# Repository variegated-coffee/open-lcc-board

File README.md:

# Open LCC Board

Schematics and PCB files for the main Open LCC hardware. Licensed under the CERN OHL-P license.

This is an evolution of [magnusnordlander/smart-lcc](https://github.com/magnusnordlander/smart-lcc).

## Disclaimer

Anything you do with this, you do at your own risk. Components have been fried already during the course of this project. Your machine uses both line voltage power, high pressured hot water, steam and other dangerous components. Risks include but are not limited to, damaging the machine, personal injury, property damage and summoning dead Cthulhu from his sleep at R'lyeh.

## Architecture and feature set

* RP2040 MCU communicating over UART with the Control Board
  * 2 MB Program Flash
  * 2 MB Settings Flash
  * Micro SD Card Slot
  * 2x QWIIC expansion ports
* ESP32-S3-WROOM-1U-N16R8 MCU
  * Connector for SSD1309 128x64px OLED display (only one display can be used at a time)
  * Solder pads for ST9987V 1.47" Round Rectangle TFT display (only one display can be used at a time)
  * Two push buttons
  * 1x QWIIC expansion port
  * Antenna connector (Espresso machines are basically faraday cages, so an external antenna is a good idea)
* 5 wire bus between RP2040 and ESP32-S3
	* RX, TX, CTS, RTS, Serial Boot
* Debug port
  * Exposes RP2040 USB, RP2040 SWD, RP2040 BOOTSEL, RP2040 ~RESET, ESP32 USB, ESP32 JTAG, ESP32 GPIO0, ESP32 EN and power rails.

## Hardware revisions

### Smart LCC (various revisions, not maintained in this repository)

The earliest revisions of this board. Based around Arduino RP2040 Nano.

### R1A (r1a branch)

This design is NOT RECOMMENDED for any purpose. It relies on the Control Board providing 3V3 to the board, but the Control Board is not able to supply enough power. As such, it *does not work as intended*. 

It is however a major redesign from the Smart LCC, and added most of the features described above.

### R2A (r2a branch)

Latest manufactured revision, though if you want one of the boards, you may want to wait for R2B.

#### Changes from R1A

* Added I2C pull-up resistors for QWIIC expansion ports
* Added on-board DC-DC converter to step down 12V to 3V3.
* Added back side connector for 1.47" TFT
* Moved test points for display connector to back side
* Added full bus to RP2040 settings flash (n.b. not the program flash), allowing for QSPI via PIO instead of regular SPI
* Added QWIIC expansion port to ESP32-S3
* Added Test Points for unused RP2040 GPIOs
* Removed 3V3_OLED from debug port

#### Errata

* The Schottky diodes do not provide adequate power supply reverse current protection. **DO NOT SUPPLY POWER FROM BOTH A DEBUG BOARD AND A CONTROL BOARD SIMULTANEOUSLY**
* It is unnecessary to connect both SD_DET_A and SD_DET_B to an MCU.

### R2B (r2b branch)

This revision hasn't been completely manufactured, and I don't intend to ever do that. I did order PCBs and verify the OR-ing controller subcircuit though, which is why there's now a R2C.

#### Changes from R2A

* Replaced the Schottky Diodes with two LM5050-1 OR-ing controllers.
* Connected SD card DET_A to GND, and removed the connection from the RP2040. 
* Widened traces and trace clearances, and added copper pours for improved manufacturability.

#### Errata

* The LM5050-1 and the MOSFET have reverse leakage currents totalling 0.6 mA. While this is unlikely to cause any issues in the real world, adding pulldown resistors seems prudent.

### R2C (main branch)

This revision hasn't been completely manufactured either (I'm running R2A in my machine), and as of writing, I don't have any plans to do so. Considering the small changes from R2B and R2A, which have been partially verified and fully verified respectively though, everything should work a treat.

#### Changes from R2B

* Added 18K7 pulldown resistors to the power supply rails.

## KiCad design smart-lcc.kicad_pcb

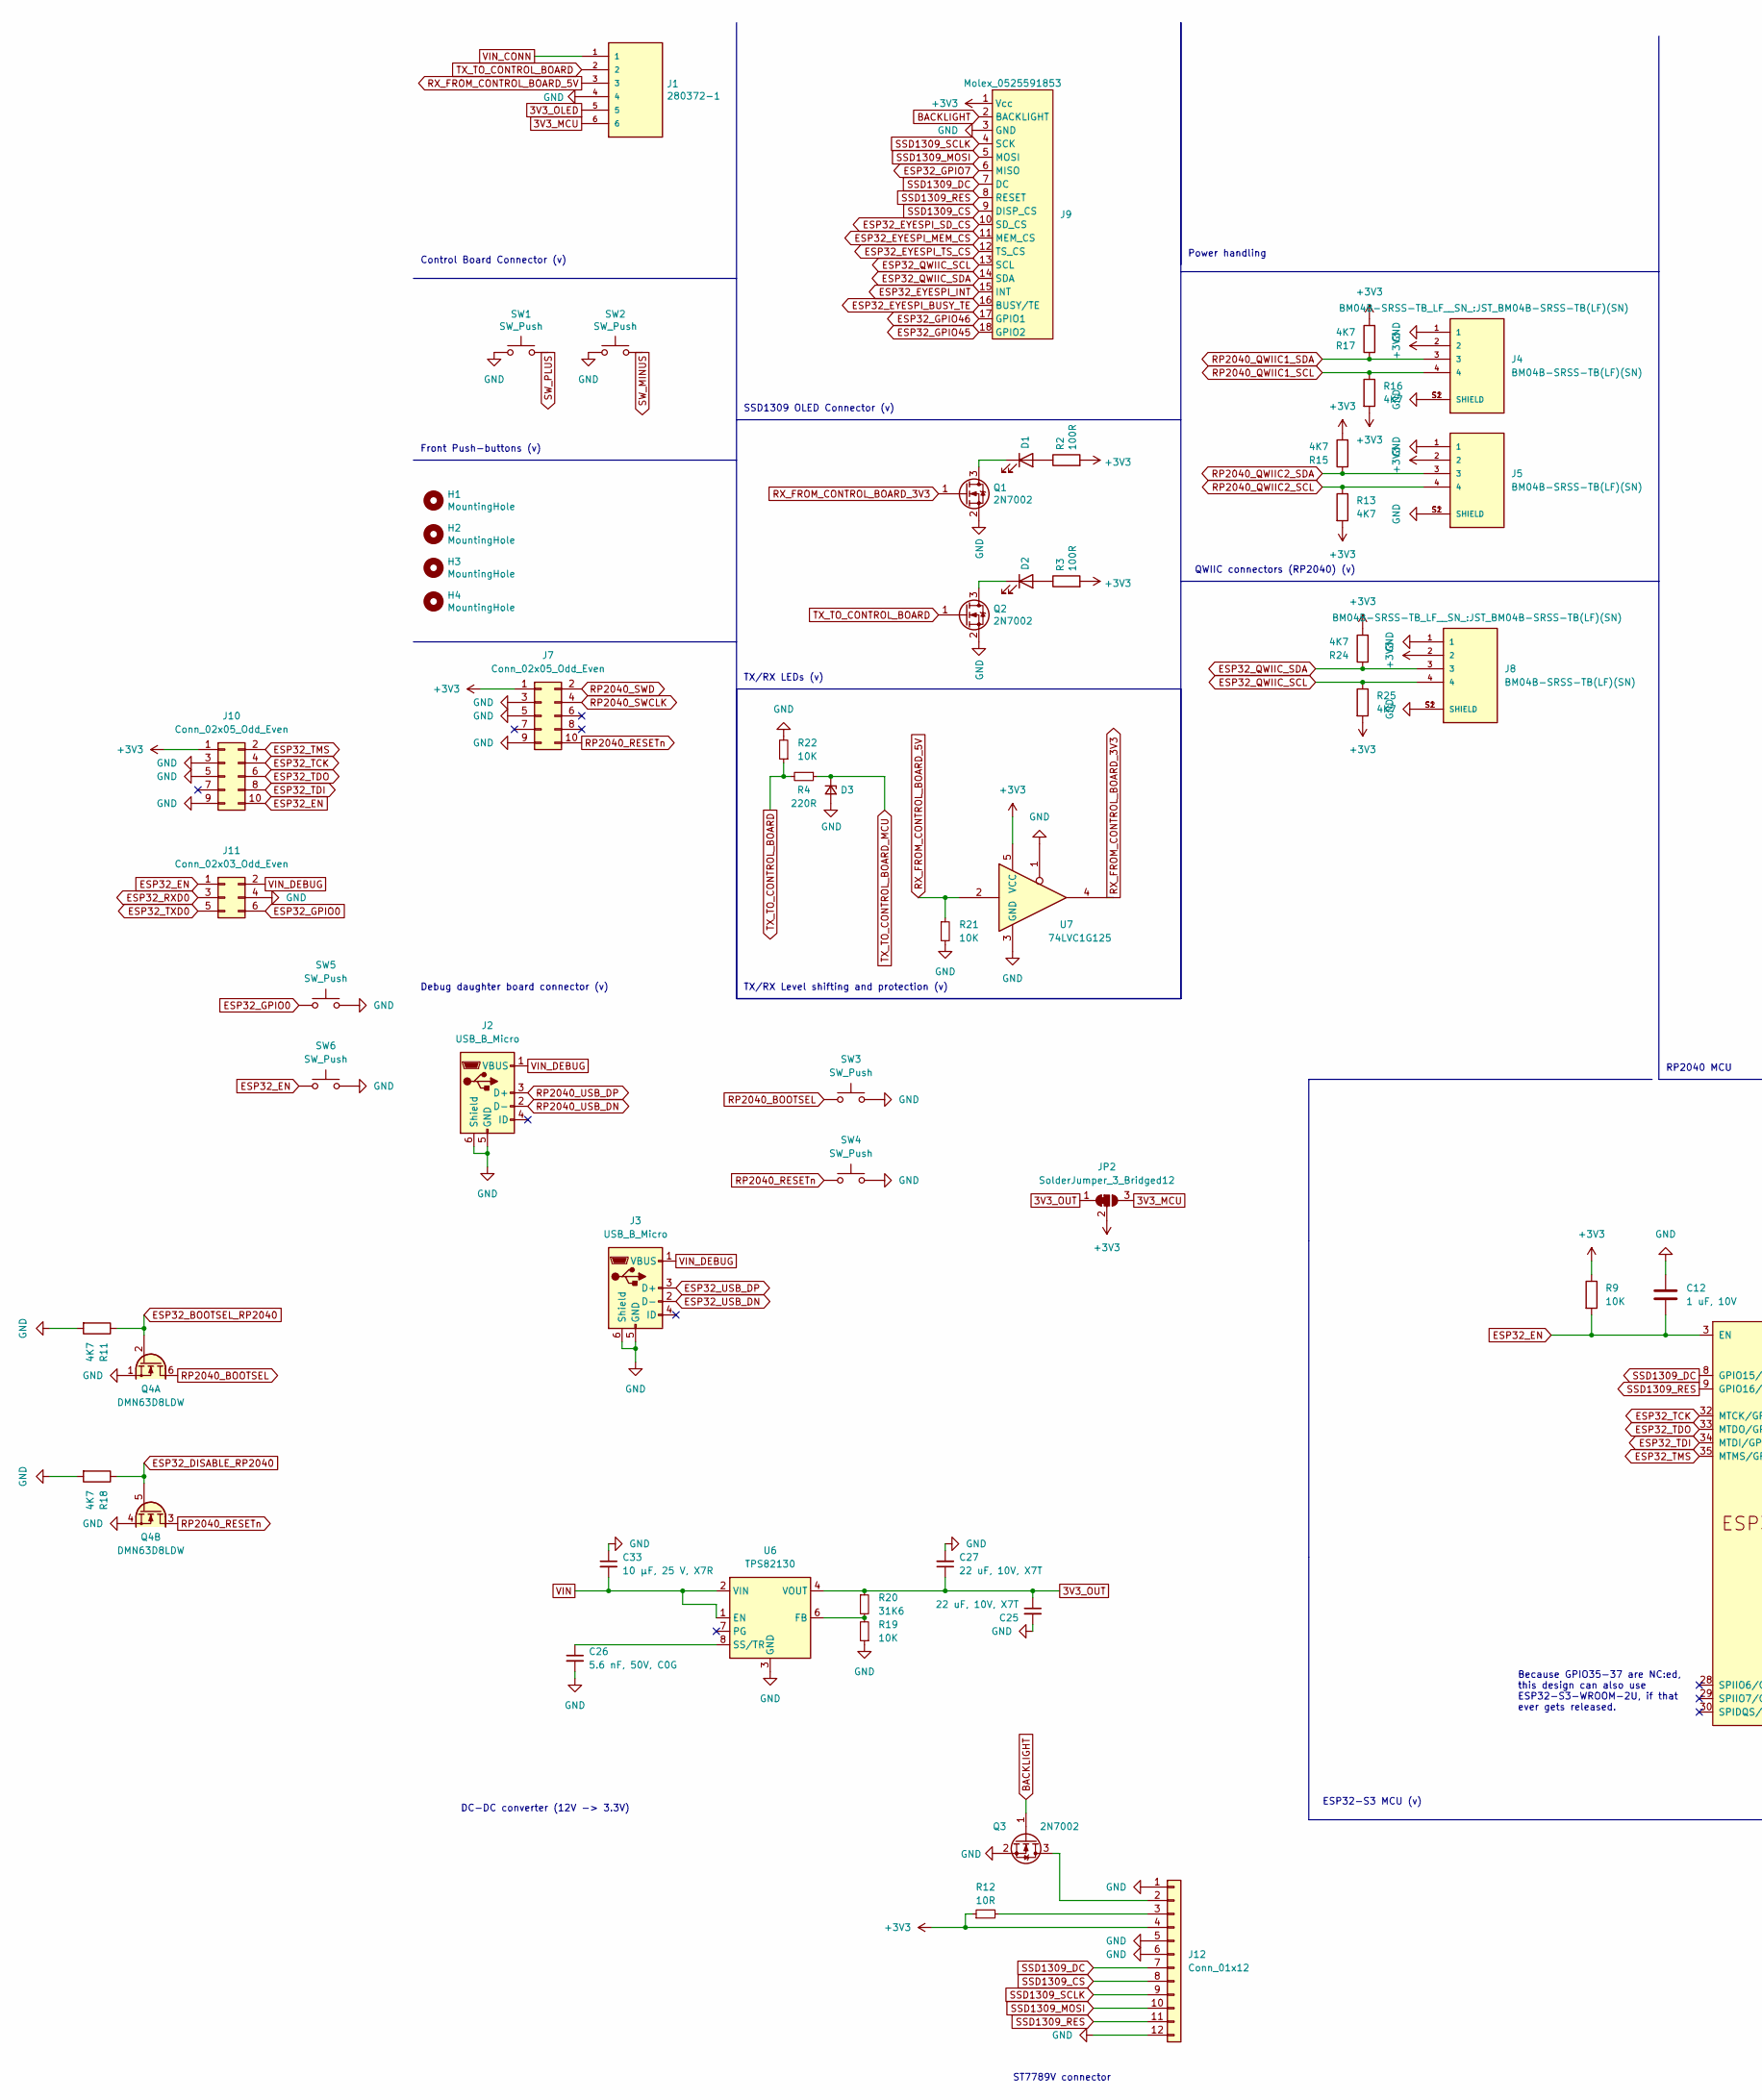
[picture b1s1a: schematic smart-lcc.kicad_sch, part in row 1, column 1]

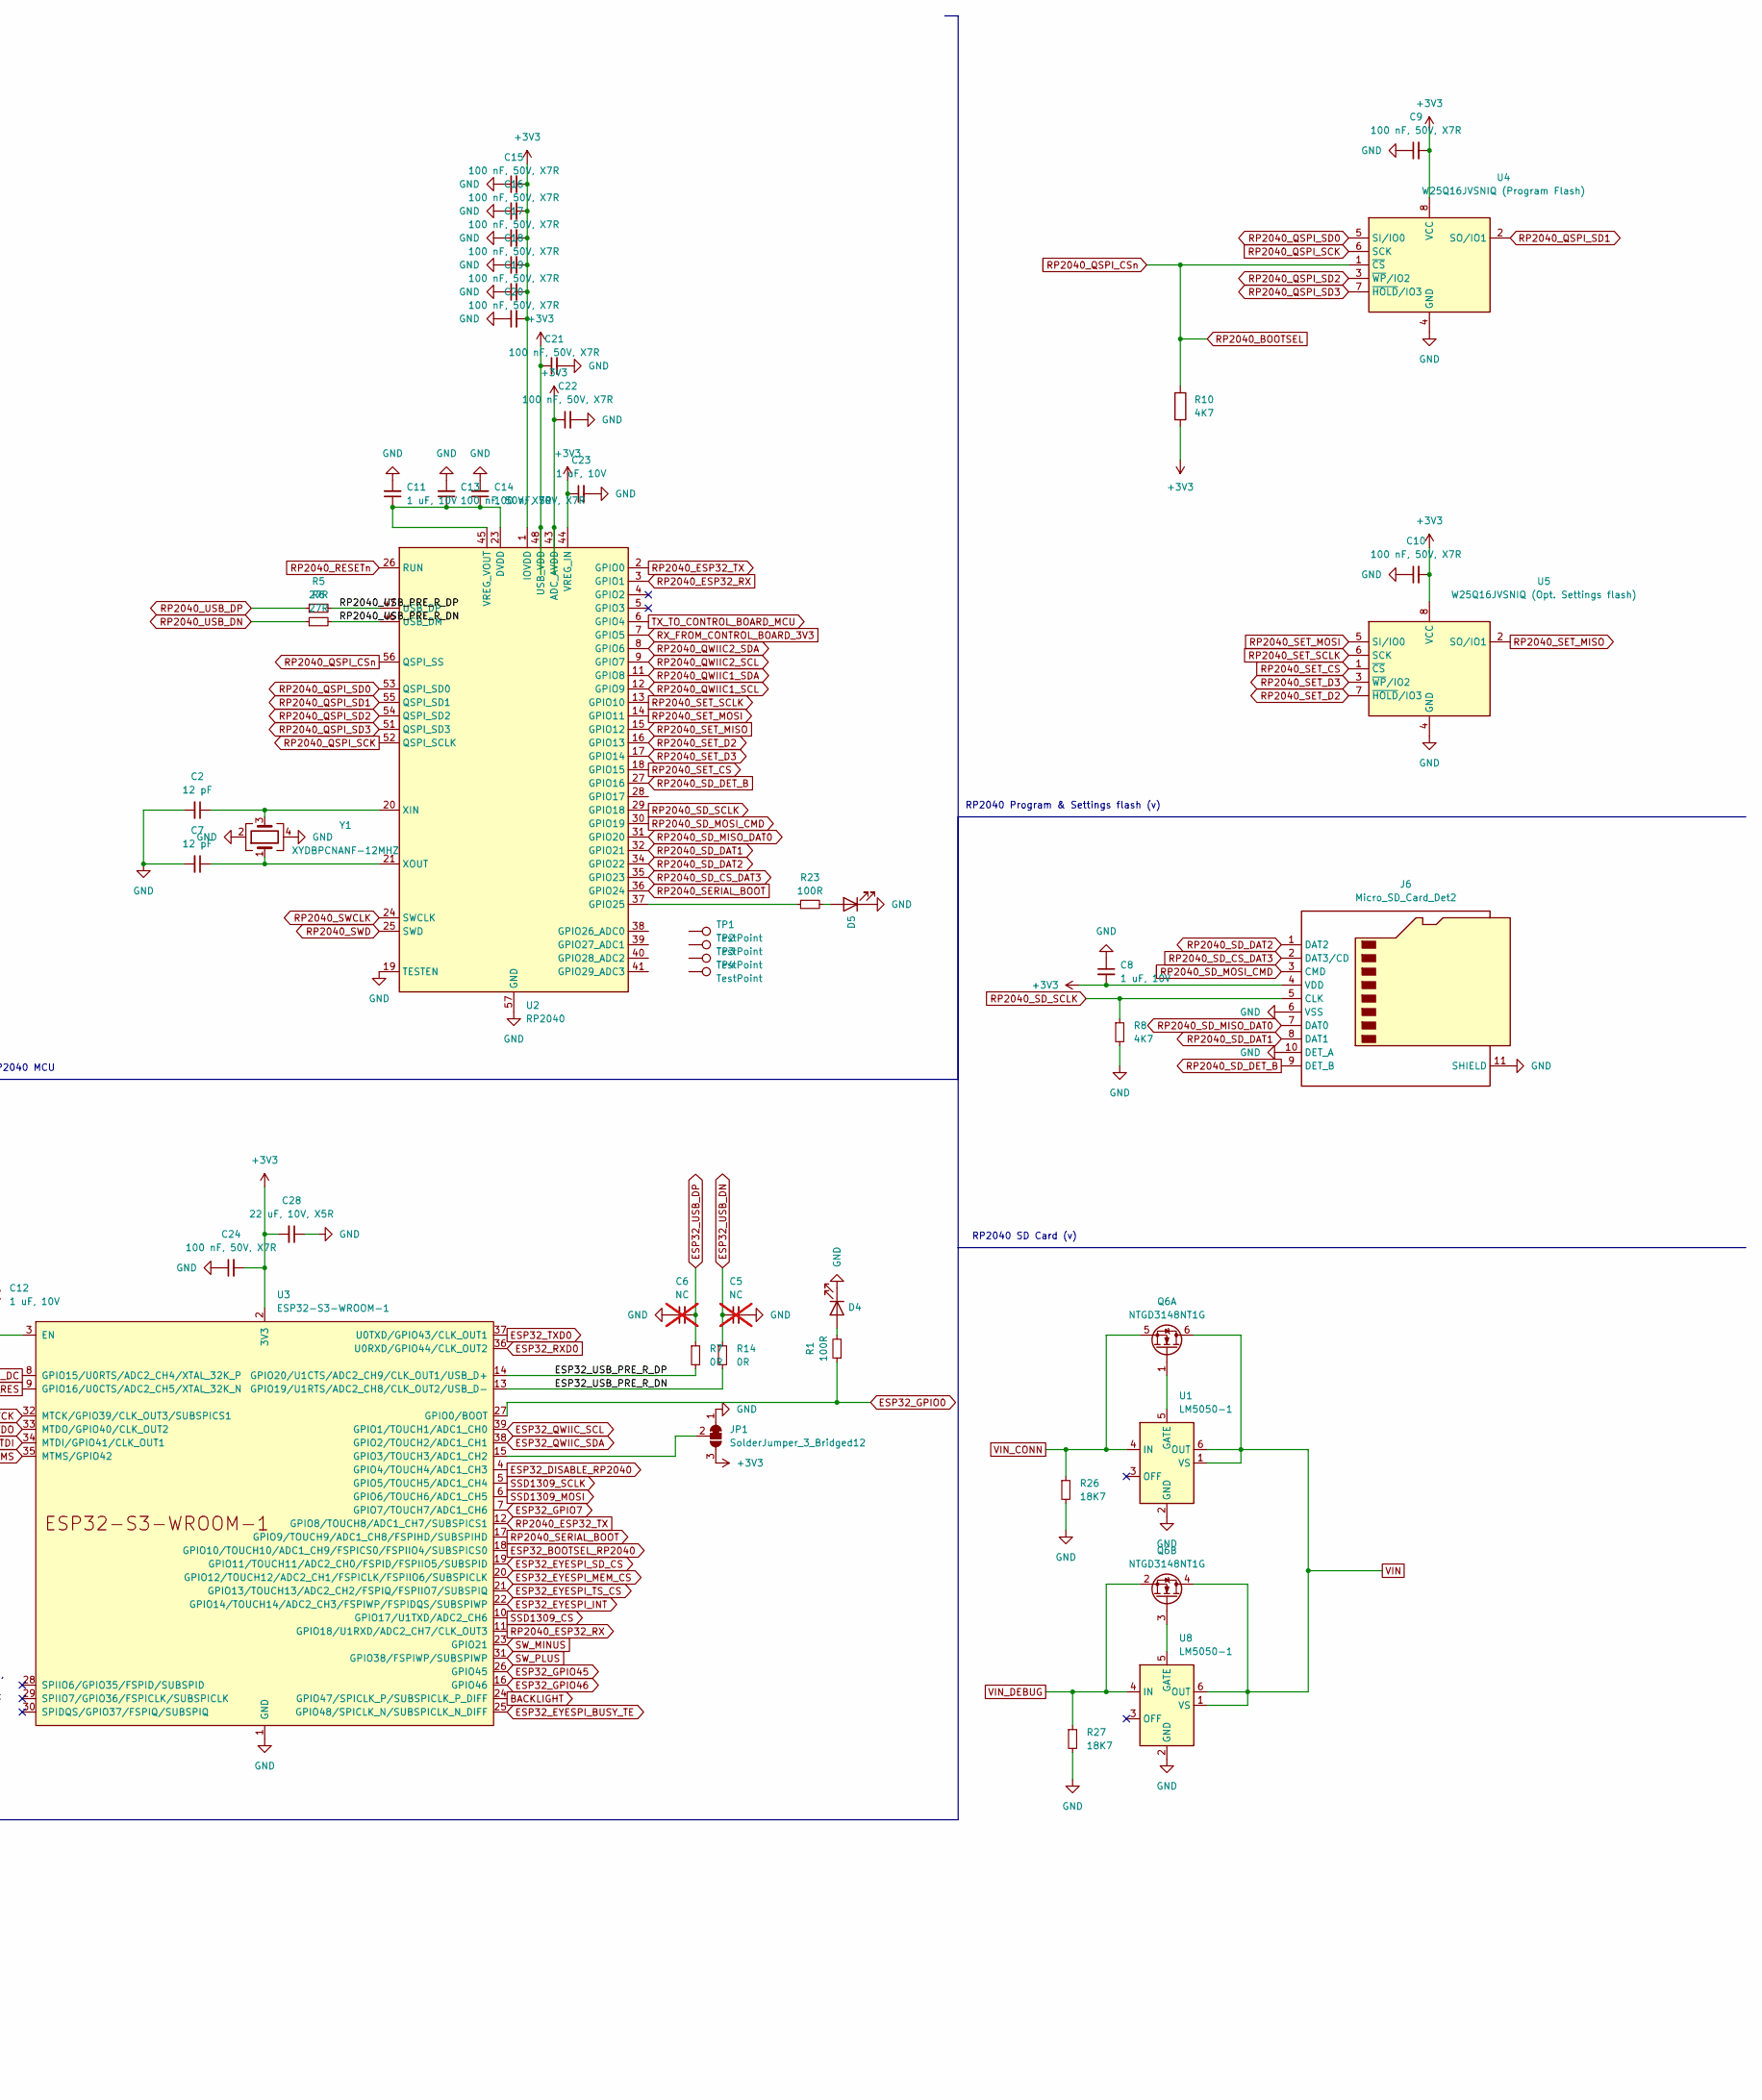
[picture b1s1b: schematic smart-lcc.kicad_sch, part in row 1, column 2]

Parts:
C2, C7: 12 pF; C_0402_1005Metric; LCSC C161527
C5, C6: NC; C_0402_1005Metric; not fitted
C8: 1 uF, 10V; C_0201_0603Metric; LCSC C426073
C9, C10, C13, C14, C15, C16, C17, C18, C19, C20, C21, C22, C24: 100 nF, 50V, X7R; C_0201_0603Metric; JLCPCB Basic N
C11, C12, C23: 1 uF, 10V; C_0201_0603Metric; JLCPCB Basic N
C25, C27: 22 uF, 10V, X7T; C_0805_2012Metric; LCSC C782176
C26: 5.6 nF, 50V, C0G; C_0402_1005Metric; LCSC C2976066
C28: 22 uF, 10V, X5R; C_0603_1608Metric; LCSC C2980159
C33: 10 μF, 25 V, X7R; C_1206_3216Metric; LCSC C2803388
D1, D2, D4, D5: 19-217/BHC-ZL1M2RY/3T; LED_0603_1608Metric; JLCPCB Basic Y
D3: TPZ3V6C-1006; D_SOD-882_DFN1006-2; JLCPCB Basic N
H1, H2, H3, H4: MountingHole; MountingHole_2.7mm
J1: 280372-1; TE_280372-1
J2, J3: USB_B_Micro; USB_Micro-B_Molex-105133-0001; LCSC C586226
J4, J5, J8: BM04B-SRSS-TB(LF)(SN); JST_BM04B-SRSS-TB(LF)(SN); PARTREV N/A; LCSC C160390
J6: Micro_SD_Card_Det2; microSD_HC_Hirose_DM3D-SF; JLCPCB Basic N
J7, J10: Conn_02x05_Odd_Even; PinHeader_2x05_P1.27mm_Vertical_SMD
J9: Molex_0525591853; CON_5051101892_MOL; LCSC C3169221
J11: Conn_02x03_Odd_Even; PinHeader_2x03_P1.27mm_Vertical_SMD
J12: Conn_01x12; TFT_1.47IN_172X320_12P
JP1: SolderJumper_3_Bridged12; SolderJumper-3_P1.3mm_Bridged2Bar12_RoundedPad1.0x1.5mm_Num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
JP2: SolderJumper_3_Bridged12; SolderJumper-3_P1.3mm_Bridged2Bar12_RoundedPad1.0x1.5mm
Q1, Q2, Q3: 2N7002; SOT-23; JLCPCB Basic Y
Q4: DMN63D8LDW; SOT-363_SC-70-6; LCSC C211422
Q6: NTGD3148NT1G; TSOP-6_1.65x3.05mm_P0.95mm; LCSC C77713
R1, R2, R3, R23: 100R; R_0201_0603Metric; LCSC C2935235
R4: 220R; R_0201_0603Metric; JLCPCB Basic N
R5, R6: 27R; R_0201_0603Metric; LCSC C321419
R7, R14: 0R; R_0201_0603Metric; JLCPCB Basic N
R8, R10, R11, R13, R15, R16, R17, R18, R24, R25: 4K7; R_0201_0603Metric; JLCPCB Basic N
R9: 10K; R_0201_0603Metric; JLCPCB Basic Y
R12: 10R; R_0201_0603Metric; LCSC C851817
R19, R21, R22: 10K; R_0201_0603Metric; LCSC C25744
R20: 31K6; R_0201_0603Metric; LCSC C2986236
R26, R27: 18K7; R_0201_0603Metric; LCSC C102855
SW1, SW2: SW_Push; ADTSMW65
SW3, SW4, SW5, SW6: SW_Push; SW4_PTS815 SJM 250 SMTR LFS_CNK; LCSC C2689510
TP1, TP2, TP3, TP4: TestPoint; TestPoint_Pad_D1.5mm
U1, U8: LM5050-1; TSOT-23-6; LCSC C473393
U2: RP2040; QFN-56-1EP_7x7mm_P0.4mm_EP3.2x3.2mm; JLCPCB Basic N
U3: ESP32-S3-WROOM-1; ESP32-S3-WROOM-1U; JLCPCB Basic N
U4: W25Q16JVSNIQ (Program Flash); SON50P300X200X60-9N; LCSC C2843335
U5: W25Q16JVSNIQ (Opt. Settings flash); SON50P300X200X60-9N; LCSC C2843335
U6: TPS82130; Texas_SIL0008D_MicroSiP-8-1EP_2.8x3mm_P0.65mm_EP1.1x1.9mm_T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; LCSC C473914
U7: 74LVC1G125; SOT-23-5; LCSC C23654
Y1: XYDBPCNANF-12MHZ; Crystal_SMD_2520-4Pin_2.5x2.0mm; LCSC C521567

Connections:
3V3_MCU: J1.6, JP2.3 (B)
3V3_OLED: J1.5
3V3_OUT: C25.1, C27.1, JP2.1 (A), R20.1, U6.4 (VOUT), U6.5 (VOUT)
+3V3: C8.2, C9.2, C10.2, C15.2, C16.2, C17.2, C18.2, C19.2, C20.2, C21.1, C22.1, C23.1, C24.2, C28.2, J4.2, J5.2, J6.4 (VDD), J7.1, J8.2, J9.1 (Vcc), J10.1, J12.4, JP1.3 (B), JP2.2 (C), R2.2, R3.2, R9.1, R10.2, R12.1, R13.2, R15.2, R16.2, R17.2, R24.2, R25.2, U2.1 (IOVDD), U2.10 (IOVDD), U2.22 (IOVDD), U2.33 (IOVDD), U2.42 (IOVDD), U2.43 (ADC_AVDD), U2.44 (VREG_IN), U2.48 (USB_VDD), U2.49 (IOVDD), U3.2 (3V3), U4.8 (VCC), U5.8 (VCC), U7.5 (VCC)
/ESP32_USB_PRE_R_DN: R14.2, U3.13 (GPIO19/U1RTS/ADC2_CH8/CLK_OUT2/USB_D-)
/ESP32_USB_PRE_R_DP: R7.2, U3.14 (GPIO20/U1CTS/ADC2_CH9/CLK_OUT1/USB_D+)
/RP2040_USB_PRE_R_DN: R6.2, U2.46 (USB_DM)
/RP2040_USB_PRE_R_DP: R5.2, U2.47 (USB_DP)
BACKLIGHT: J9.2 (BACKLIGHT), Q3.1 (G), U3.24 (GPIO47/SPICLK_P/SUBSPICLK_P_DIFF)
ESP32_BOOTSEL_RP2040: Q4.2 (G1), R11.1, U3.18 (GPIO10/TOUCH10/ADC1_CH9/FSPICS0/FSPIIO4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)
ESP32_DISABLE_RP2040: Q4.5 (G2), R18.1, U3.4 (GPIO4/TOUCH4/ADC1_CH3)
ESP32_EN: C12.2, J10.10, J11.1, R9.2, SW6.1, U3.3 (EN)
ESP32_EYESPI_BUSY_TE: J9.16 (BUSY/TE), U3.25 (GPIO48/SPICLK_N/SUBSPICLK_N_DIFF)
ESP32_EYESPI_INT: J9.15 (INT), U3.22 (GPIO14/TOUCH14/ADC2_CH3/FSPIWP/FSPIDQS/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)
ESP32_EYESPI_MEM_CS: J9.11 (MEM_CS), U3.20 (GPIO12/TOUCH12/ADC2_CH1/FSPICLK/FSPIIO6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)
ESP32_EYESPI_SD_CS: J9.10 (SD_CS), U3.19 (GPIO11/TOUCH11/ADC2_CH0/FSPID/FSPIIO5/S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)
ESP32_EYESPI_TS_CS: J9.12 (TS_CS), U3.21 (GPIO13/TOUCH13/ADC2_CH2/FSPIQ/FSPIIO7/S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)
ESP32_GPIO0: J11.6, R1.1, SW5.1, U3.27 (GPIO0/BOOT)
ESP32_GPIO7: J9.6 (MISO), U3.7 (GPIO7/TOUCH7/ADC1_CH6)
ESP32_GPIO45: J9.18 (GPIO2), U3.26 (GPIO45)
ESP32_GPIO46: J9.17 (GPIO1), U3.16 (GPIO46)
ESP32_QWIIC_SCL: J8.4, J9.13 (SCL), R25.1, U3.39 (GPIO1/TOUCH1/ADC1_CH0)
ESP32_QWIIC_SDA: J8.3, J9.14 (SDA), R24.1, U3.38 (GPIO2/TOUCH2/ADC1_CH1)
ESP32_RXD0: J11.3, U3.36 (U0RXD/GPIO44/CLK_OUT2)
ESP32_TCK: J10.4, U3.32 (MTCK/GPIO39/CLK_OUT3/SUBSPICS1)
ESP32_TDI: J10.8, U3.34 (MTDI/GPIO41/CLK_OUT1)
ESP32_TDO: J10.6, U3.33 (MTDO/GPIO40/CLK_OUT2)
ESP32_TMS: J10.2, U3.35 (MTMS/GPIO42)
ESP32_TXD0: J11.5, U3.37 (U0TXD/GPIO43/CLK_OUT1)
ESP32_USB_DN: C5.1, J3.2 (D-), R14.1
ESP32_USB_DP: C6.2, J3.3 (D+), R7.1
GND: C2.2, C5.2, C6.1, C7.2, C8.1, C9.1, C10.1, C11.2, C12.1, C13.2, C14.2, C15.1, C16.1, C17.1, C18.1, C19.1, C20.1, C21.2, C22.2, C23.2, C24.1, C25.2, C26.2, C27.2, C28.1, C33.1, D3.2 (A), D4.1 (K), D5.1 (K), J1.4, J2.5 (GND), J2.6 (Shield), J3.5 (GND), J3.6 (Shield), J4.1, J4.S1 (SHIELD), J4.S2 (SHIELD), J5.1, J5.S1 (SHIELD), J5.S2 (SHIELD), J6.6 (VSS), J6.10 (DET_A), J6.11 (SHIELD), J7.3, J7.5, J7.9, J8.1, J8.S1 (SHIELD), J8.S2 (SHIELD), J9.3 (GND), J10.3, J10.5, J10.9, J11.4, J12.1, J12.5, J12.6, J12.12, JP1.1 (A), Q1.2 (S), Q2.2 (S), Q3.2 (S), Q4.1 (S1), Q4.4 (S2), R8.2, R11.2, R18.2, R19.1, R21.2, R22.2, R26.2, R27.2, SW1.1, SW2.1, SW3.2, SW4.2, SW5.2, SW6.2, U1.2 (GND), U2.19 (TESTEN), U2.57 (GND), U3.1 (GND), U3.40 (GND), U3.41 (GND), U4.4 (GND), U5.4 (GND), U6.3 (GND), U6.9 (GND), U7.1, U7.3 (GND), U8.2 (GND), Y1.2, Y1.4
unnamed: D1.2 (A), R2.1
unnamed: D1.1 (K), Q1.3 (D)
unnamed: D2.2 (A), R3.1
unnamed: D2.1 (K), Q2.3 (D)
unnamed: D4.2 (A), R1.2
unnamed: D5.2 (A), R23.2
unnamed: J12.2, Q3.3 (D)
unnamed: J12.3, R12.2
unnamed: JP1.2 (C), U3.15 (GPIO3/TOUCH3/ADC1_CH2)
unnamed: Q6.1 (G), U1.5 (GATE)
unnamed: Q6.3 (G), U8.5 (GATE)
unnamed: R23.1, U2.37 (GPIO25)
unnamed: C11.1, C13.1, C14.1, U2.23 (DVDD), U2.45 (VREG_VOUT), U2.50 (DVDD)
unnamed: C2.1, U2.20 (XIN), Y1.3
unnamed: C7.1, U2.21 (XOUT), Y1.1
unnamed: R19.2, R20.2, U6.6 (FB)
unnamed: C26.1, U6.8 (SS/TR)
RP2040_BOOTSEL: Q4.6 (D1), R10.1, SW3.1, U2.56 (QSPI_SS), U4.1 (~CS)
RP2040_ESP32_RX: U2.3 (GPIO1), U3.11 (GPIO18/U1RXD/ADC2_CH7/CLK_OUT3)
RP2040_ESP32_TX: U2.2 (GPIO0), U3.12 (GPIO8/TOUCH8/ADC1_CH7/SUBSPICS1)
RP2040_QSPI_SCK: U2.52 (QSPI_SCLK), U4.6 (SCK)
RP2040_QSPI_SD0: U2.53 (QSPI_SD0), U4.5 (SI/IO0)
RP2040_QSPI_SD1: U2.55 (QSPI_SD1), U4.2 (SO/IO1)
RP2040_QSPI_SD2: U2.54 (QSPI_SD2), U4.3 (~WP/IO2)
RP2040_QSPI_SD3: U2.51 (QSPI_SD3), U4.7 (~HOLD/IO3)
RP2040_QWIIC1_SCL: J4.4, R16.1, U2.12 (GPIO9)
RP2040_QWIIC1_SDA: J4.3, R17.1, U2.11 (GPIO8)
RP2040_QWIIC2_SCL: J5.4, R13.1, U2.9 (GPIO7)
RP2040_QWIIC2_SDA: J5.3, R15.1, U2.8 (GPIO6)
RP2040_RESETn: J7.10, Q4.3 (D2), SW4.1, U2.26 (RUN)
RP2040_SD_CS_DAT3: J6.2 (DAT3/CD), U2.35 (GPIO23)
RP2040_SD_DAT1: J6.8 (DAT1), U2.32 (GPIO21)
RP2040_SD_DAT2: J6.1 (DAT2), U2.34 (GPIO22)
RP2040_SD_DET_B: J6.9 (DET_B), U2.27 (GPIO16)
RP2040_SD_MISO_DAT0: J6.7 (DAT0), U2.31 (GPIO20)
RP2040_SD_MOSI_CMD: J6.3 (CMD), U2.30 (GPIO19)
RP2040_SD_SCLK: J6.5 (CLK), R8.1, U2.29 (GPIO18)
RP2040_SERIAL_BOOT: U2.36 (GPIO24), U3.17 (GPIO9/TOUCH9/ADC1_CH8/FSPIHD/SUBSPIHD)
RP2040_SET_CS: U2.18 (GPIO15), U5.1 (~CS)
RP2040_SET_D2: U2.16 (GPIO13), U5.7 (~HOLD/IO3)
RP2040_SET_D3: U2.17 (GPIO14), U5.3 (~WP/IO2)
RP2040_SET_MISO: U2.15 (GPIO12), U5.2 (SO/IO1)
RP2040_SET_MOSI: U2.14 (GPIO11), U5.5 (SI/IO0)
RP2040_SET_SCLK: U2.13 (GPIO10), U5.6 (SCK)
RP2040_SWCLK: J7.4, U2.24 (SWCLK)
RP2040_SWD: J7.2, U2.25 (SWD)
RP2040_USB_DN: J2.2 (D-), R6.1
RP2040_USB_DP: J2.3 (D+), R5.1
RX_FROM_CONTROL_BOARD_3V3: Q1.1 (G), U2.7 (GPIO5), U7.4
RX_FROM_CONTROL_BOARD_5V: J1.3, R21.1, U7.2
SSD1309_CS: J9.9 (DISP_CS), J12.8, U3.10 (GPIO17/U1TXD/ADC2_CH6)
SSD1309_DC: J9.7 (DC), J12.7, U3.8 (GPIO15/U0RTS/ADC2_CH4/XTAL_32K_P)
SSD1309_MOSI: J9.5 (MOSI), J12.10, U3.6 (GPIO6/TOUCH6/ADC1_CH5)
SSD1309_RES: J9.8 (RESET), J12.11, U3.9 (GPIO16/U0CTS/ADC2_CH5/XTAL_32K_N)
SSD1309_SCLK: J9.4 (SCK), J12.9, U3.5 (GPIO5/TOUCH5/ADC1_CH4)
SW_MINUS: SW2.2, U3.23 (GPIO21)
SW_PLUS: SW1.2, U3.31 (GPIO38/FSPIWP/SUBSPIWP)
TX_TO_CONTROL_BOARD: J1.2, Q2.1 (G), R4.2, R22.1
TX_TO_CONTROL_BOARD_MCU: D3.1 (K), R4.1, U2.6 (GPIO4)
VIN: C33.2, Q6.4 (D), Q6.6 (D), U1.1 (VS), U1.6 (OUT), U6.1 (EN), U6.2 (VIN), U8.1 (VS), U8.6 (OUT)
VIN_CONN: J1.1, Q6.5 (S), R26.1, U1.4 (IN)
VIN_DEBUG: J2.1 (VBUS), J3.1 (VBUS), J11.2, Q6.2 (S), R27.1, U8.4 (IN)

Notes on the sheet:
Power handling
RP2040 Program & Settings flash (v)
TX/RX LEDs (v)
RP2040 MCU
TX/RX Level shifting and protection (v)
DC-DC converter (12V -> 3.3V)
ESP32-S3 MCU (v)
Control Board Connector (v)
ST7789V connector
RP2040 SD Card (v)
Front Push-buttons (v)
SSD1309 OLED Connector (v)
Because GPIO35-37 are NC:ed, this design can also use ESP32-S3-WROOM-2U, if that ever gets released.
Debug daughter board connector (v)
QWIIC connectors (RP2040) (v)

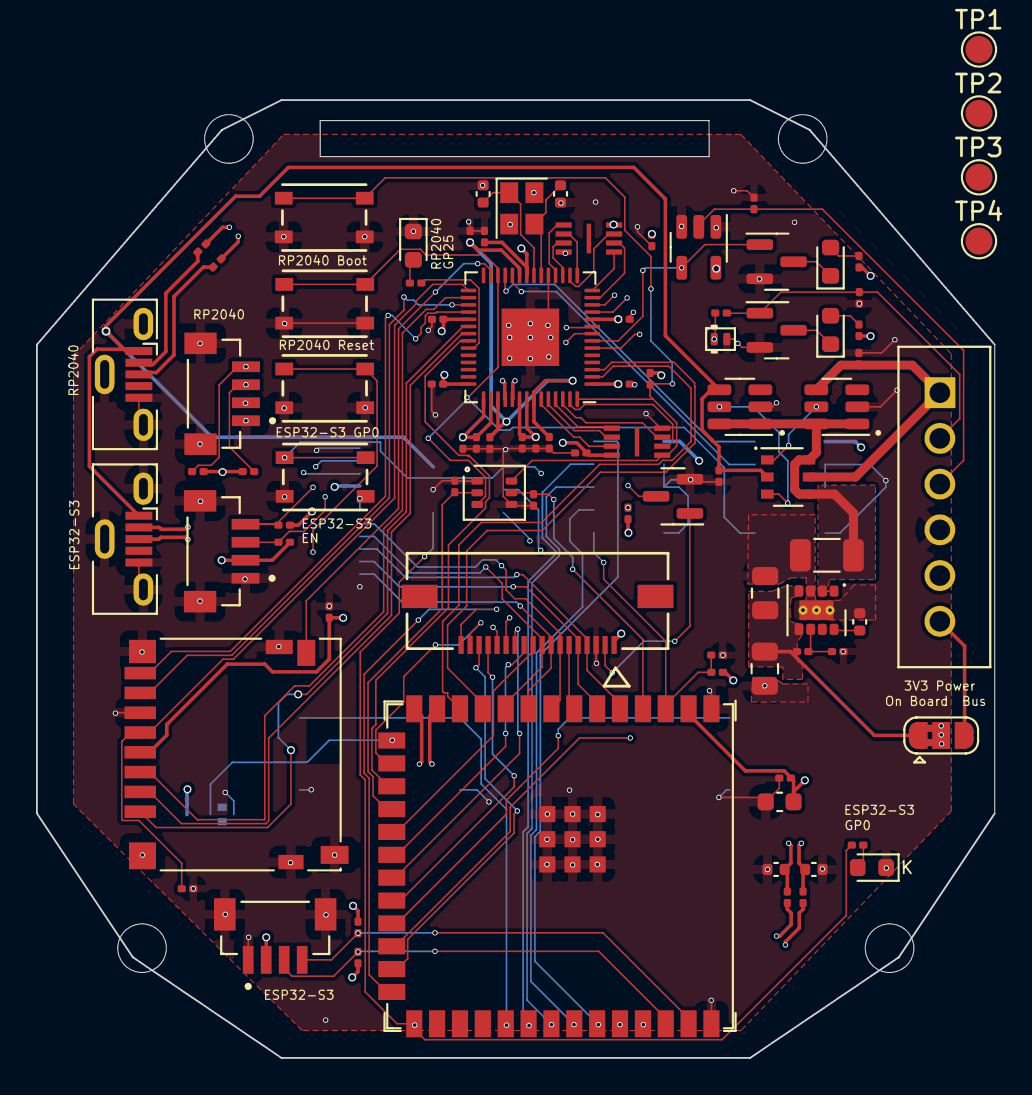
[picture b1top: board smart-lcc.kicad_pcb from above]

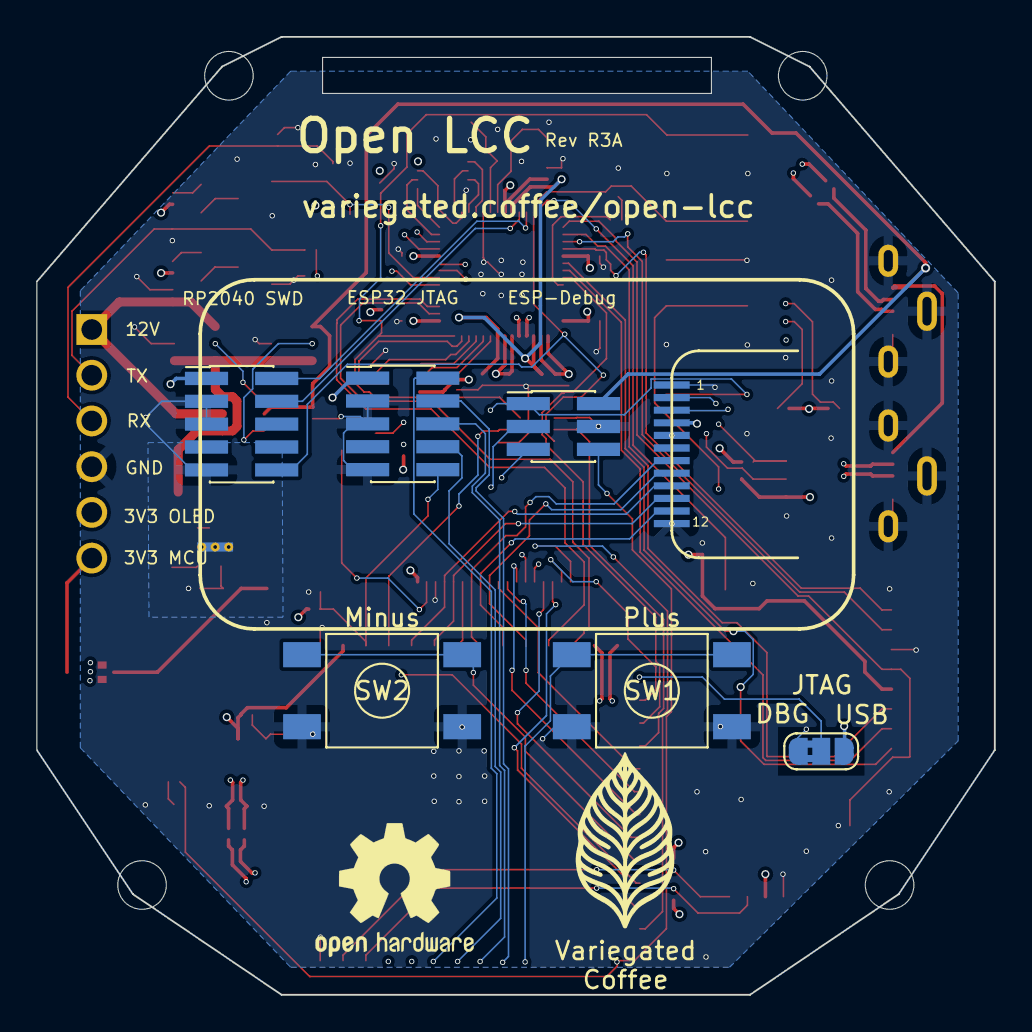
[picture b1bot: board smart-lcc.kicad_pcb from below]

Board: 6 copper layers, 53.2 x 53.2 mm, 100 parts (7 on the bottom side), 93 nets.

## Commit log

2023-10-30 R2A WIP
2023-10-30 Initial work on R2B
2023-10-31 Removed SD_DET_A from RP2040 and connected DET_A on the SD card to GND
2023-11-03 Updated design for easier manufacturability
2023-11-03 Add licenses and README
2023-11-09 Add board photos
2023-11-16 Added revision R2C
2023-11-16 Silk screen changes
2024-02-24 Added some very basic ordering information (more soon)
2024-02-24 Added some basic manufacturing instructions
2024-02-24 Table formatting
2024-02-25 Create BOM_PCBWay.xlsx
    Tried to source as much as possible by digikey.
    passives are manufactory free
    yellow marked positions are replacements found by digikey
2024-02-27 Updated to use a more flexible FPC connector footprint
2024-06-10 R3A (preliminary)
    Changes:
    * Switched the OLED connector for an EyeSPI connector (feature parity with APEC)
    * Removed the need for a debug board by moving USB connectors and SWD/JTAG ports to this board
    * Move to 6 layers
    * Component changes for a more dense design
